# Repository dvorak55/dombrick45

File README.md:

# Dombrick45 : Dvorak Oriented 45% Keyboard

Dombrick45 is self made dvorak oriented keyboard.  
Dombrick45はDvorak配列志向の自作キーボードです。

"Dombrick" stands for Dvorak Oriented Mechanical Breakthough Remakable Interesting Coolest Keyboard (joke  
Dombrickという名前は「Dvorak志向の革新的で驚くべき大変興味深い最高にクールな機械式キーボード」を表す英単語の頭文字を取って命名しました（笑

Actually, "Dombri" means one of a japanese food style bowl, "ck" means nothing.  
嘘です、Dombriはもちろん日本語の丼を意味しており、ckの二文字はバランスを整えるために付けているだけです。

以下、[DescriptionのPDF](https://github.com/dvorak55/dombrick45/blob/master/description.pdf)から抜粋

## 概要
Dombrick45はコンパクトでシンプルな45％キーボードです。MCUもハンダ付けするタイプで比較的難易度は高め。QMK準拠、カスタマイズ可能。

## 特徴
- ボトムプレートがKitに含まれているため、キースイッチ・キーキャップとケーブルだけ揃えればキーボードが完成します
- 横幅13.25U、カーソルキーも搭載可能、USB Mini-BとUSB-Cの両対応
- 最下段キーがHotSwapで43keyから48keyまで好きに選べる。6.25uスペースバーも搭載可能
- ネジ締めは一切不要。モビロンバンドとシリコンマットによる全く新しいマウント方式なので組立しやすい
- ボトムプレートが重いので打鍵感が安定しています
- ATmega32U4やUSB-C端子のはんだ付けが必要。部品はすべて表面実装なので難易度は比較的高め
- 40%キーボード用キーキャップを使用(サンプルはGMK Jamón Forties)

## Kitに入っている部品
1. PCB 1枚
2. 電子部品(コンデンサ 7個、ダイオード 50個、フューズ 1個、抵抗 6個、ESDダイオード 1個、水晶振動子 1個、リセットスイッチ 1個)
3. MCU(ATmega32U4 1個)
4. USB端子(USB Mini-B 1個、USB-C 1個)
5. PCBソケット(Cherry MX互換 13個)
6. スタビライザー(2Uと6.25Uがそれぞれ 1個ずつ)
7. モビロンゴム(55mm 12本、100mm 6本)
8. シリコンシート(基板サイズ 2枚分)
9. ボトムプレート(厚さ2mmステンレス、基板サイズ 1枚)
10. プラスチックテープ(ソケットを隠すのに十分な長さ)
11. リセットスイッチを押す薄いプラ板

## 別途ご用意頂く部品
1. キースイッチ(Cherry MX互換で5ピンPCBマウント) 48個
2. キーキャップ
3. USBケーブル

## スペック（実装例）
サイズ：77mm × 253mm × 23mm

重さ　：約560グラム

## スイッチ互換性
Cherry MX互換とALPS(ただし最下段キーはCherry MX互換のみ)

## 写真等
### 実装例１

現在作者が使っているキー配列（48キー）。 GMK Paperworkを用いてさえ足りないキーキャップがある
### 実装例２

43キーしかない配列。6.25uのスペースバーを使えるようにしたかったんだ。

ちなみに最下段の両端のキーは取り外して、見えるはずの穴は赤色のプラスチックテープで巧妙に見えなくなっているので違和感が（多分）ないはず
### 実装例３

参考までに。無刻印は味気ない気がした。
### PCB基板（Ver.1かつJLCPCB版）

5枚のみ発注したJLCPCB版。ラーメンが食べたくなるでしょう？

Ver.1はこの5枚とALLPCBから届いた6枚、計11枚あります。
### スイッチ実装写真

右下と左下に赤色のプラスチックテープが貼ってあります。分かるかな〜

## Build Guide　ビルドガイド
部品をすべて実装するとこんな感じになります。

さぁ、あなたの丼を実装する素晴らしい一日をスタートしましょう！

### 多分必要な道具
- はんだごて　30ワットあればOK
- ハンダを拭くスポンジとはんだごて置き場
- ハンダ吸い取り器、ハンダ吸い取り線
- 鉛フリーではない普通のハンダ
- 無洗浄フラックス
- フラックスを洗浄するアルコール的なもの（ケンエーIPAとか）
- ピンセットがあると最高に便利
- 導通確認やショート確認のためのテスター
- カッター
- カッターマット

### 実装手順
1. 以下にあげた表面実装部品を基板PCBにすべてはんだ付けします。Kitの部品にはすべて部品番号が明示されています。また、PCB基板上のはんだ付けする場所に部品番号が印刷されています。すなわち、部品番号ごとに取り出した部品を、その番号の書かれた場所にはんだ付けすればOKです。ここで実装する部品は、向きが関係無い部品、もしくは向きを間違える心配のない部品です。
   - コンデンサ 7個　C1〜C7
   - ヒューズ 1個　F1
   - 抵抗 6個　R1〜R6
   - リセットスイッチ 1個　※4つ足のスイッチ　SW1
   - USB端子 2個　※USB-CとUSB-MiniBの2種類　USB1、USB2
   - ESDダイオード 1個　※4つ足の黒い部品　1本だけ足が広い。基板実装箇所でも1箇所だけ足が広い。　U2  
部品をすべて実装した写真の拡大バージョンです。こちらも参考にしてください↓

2. MCU 1個と水晶振動子 1個をはんだ付けします。向きに注意。
   - MCUの○印の位置と、PCB基板上の⚡印の位置が同じになるようにします
   - 水晶振動子は非常にわかりにくいですが、MCUから見て文字が読める向きに付けます。
MCUと水晶振動子の向きは以下の写真も参照してください↓

3. 上記部品がはんだ付け終わったら、パソコンとUSBケーブルで接続し、Dombrick45のファームウェアが書き込めるかを確認します。書き込めれば次に進み、書き込めない or 認識されなければ、はんだ付けを修正します。  
※ファームウェアを書き込む方法はこちらを参照下さい→　https://github.com/dvorak55/dombrick45/tree/master/qmk
4. ダイオードをはんだ付けします。向きはすべて線の書いてある方向が下になるようにします。スペースバーのある方が下、USB-MiniB端子のある方が上です。2個余るはずです（2個は予備です）。向きは以下の写真も参考にしてください。

5. PCBソケットをはんだ付けします。ソケットをPCB基板に差し込んでから、ハンダを付けてください。
6. 最後にキースイッチをはんだ付けします。
7. PCBソケットをはんだ付けした最下段にキースイッチを差し込みます。スペースバーのスタビライザーも取り付けます。
8. シリコンシートを基板のサイズに切り取ります。付属のシリコンシートから基板のサイズ2枚分取れます。これはPCB基板とボトムプレートの間に敷く衝撃吸収材兼絶縁材です。基板サイズのシリコンシートを2枚そのまま重ねるも良し、1枚を3分の2のところで分割し、上は3枚、中央は2枚、下は1枚と階段状にすることでキーボードに若干の角度を付けるも良し。
シリコンシートは付属のボトムプレートのサイズに切り取ります。

USB端子のある場所は、シリコンシートに切り欠けを作り、端子が干渉しないようにします。

2枚分のシリコンシートを階段状にする場合、以下のように切り欠けが重なるようにします。

このままだとリセットスイッチとシリコンシートが干渉し、強くキーを押すとリセットスイッチが押されてしまいます。そこで、リセットスイッチの位置（以下の画像の白い所）にも切り欠けを作ります。これは一番上に重ねたシートのみでOKです。

切り欠けを作ったシート

最終的にできたシートを重ねた状態

9. 基板・シリコンシート・ボトムプレートを重ねます。
10. それらをモビロンゴムでまとめます。短いモビロンゴムは縦方向、長いモビロンゴムは横方向をとめます。うまくキースイッチの間に入るようにゴムを調整します。短いゴムは4本、長いゴムは2本で足ります。残りは予備です。このゴムは滑り止めにもなっています。  
ゴムは以下の写真の線のところに配置すると良さげです。横方向の一番上はあってもなくても大丈夫です。

短いゴムはそのまま付けるだけだとキーキャップに干渉します。

適当なキーキャップを取り外し、

先の尖っていない細い棒等でモビロンゴムを一番下まで突っつきます。

4箇所ともゴムをきちんと一番下まで入れます。

横方向のゴムを付けるのは簡単だと思います。3本付けるとこのようになります。

11. お好きなキーキャップを取り付けます
12. もし43キーか46キーのキーマップを実装していた場合、最下段両端のキーソケットと穴を隠すために、Kitの袋に貼り付いている赤色のプラスチックテープを適当に切りPCB基板の最下段両端部分を隠すように貼ります。
13. お好きなUSBケーブルでパソコンに接続します
14. リセットスイッチが右手小指辺りにあります。リセットスイッチを押すための薄いプラ板をシリコンシートとPCB基板の間に挿入し、リセットスイッチを押してください  
この辺りに板を差し込みます。

リセットスイッチは以下の写真の黄色丸の位置にあります。板をこの辺りにまで差し込み、キーボードを押してリセットスイッチを押します。

15. リセットスイッチを押したら、ファームウェアを書き込み、動作確認を行う  
ファームウェアを書き込む方法はこちらを参照下さい→　https://github.com/dvorak55/dombrick45/tree/master/qmk

### 完成です！
楽しい丼生活をエンジョイしてください！

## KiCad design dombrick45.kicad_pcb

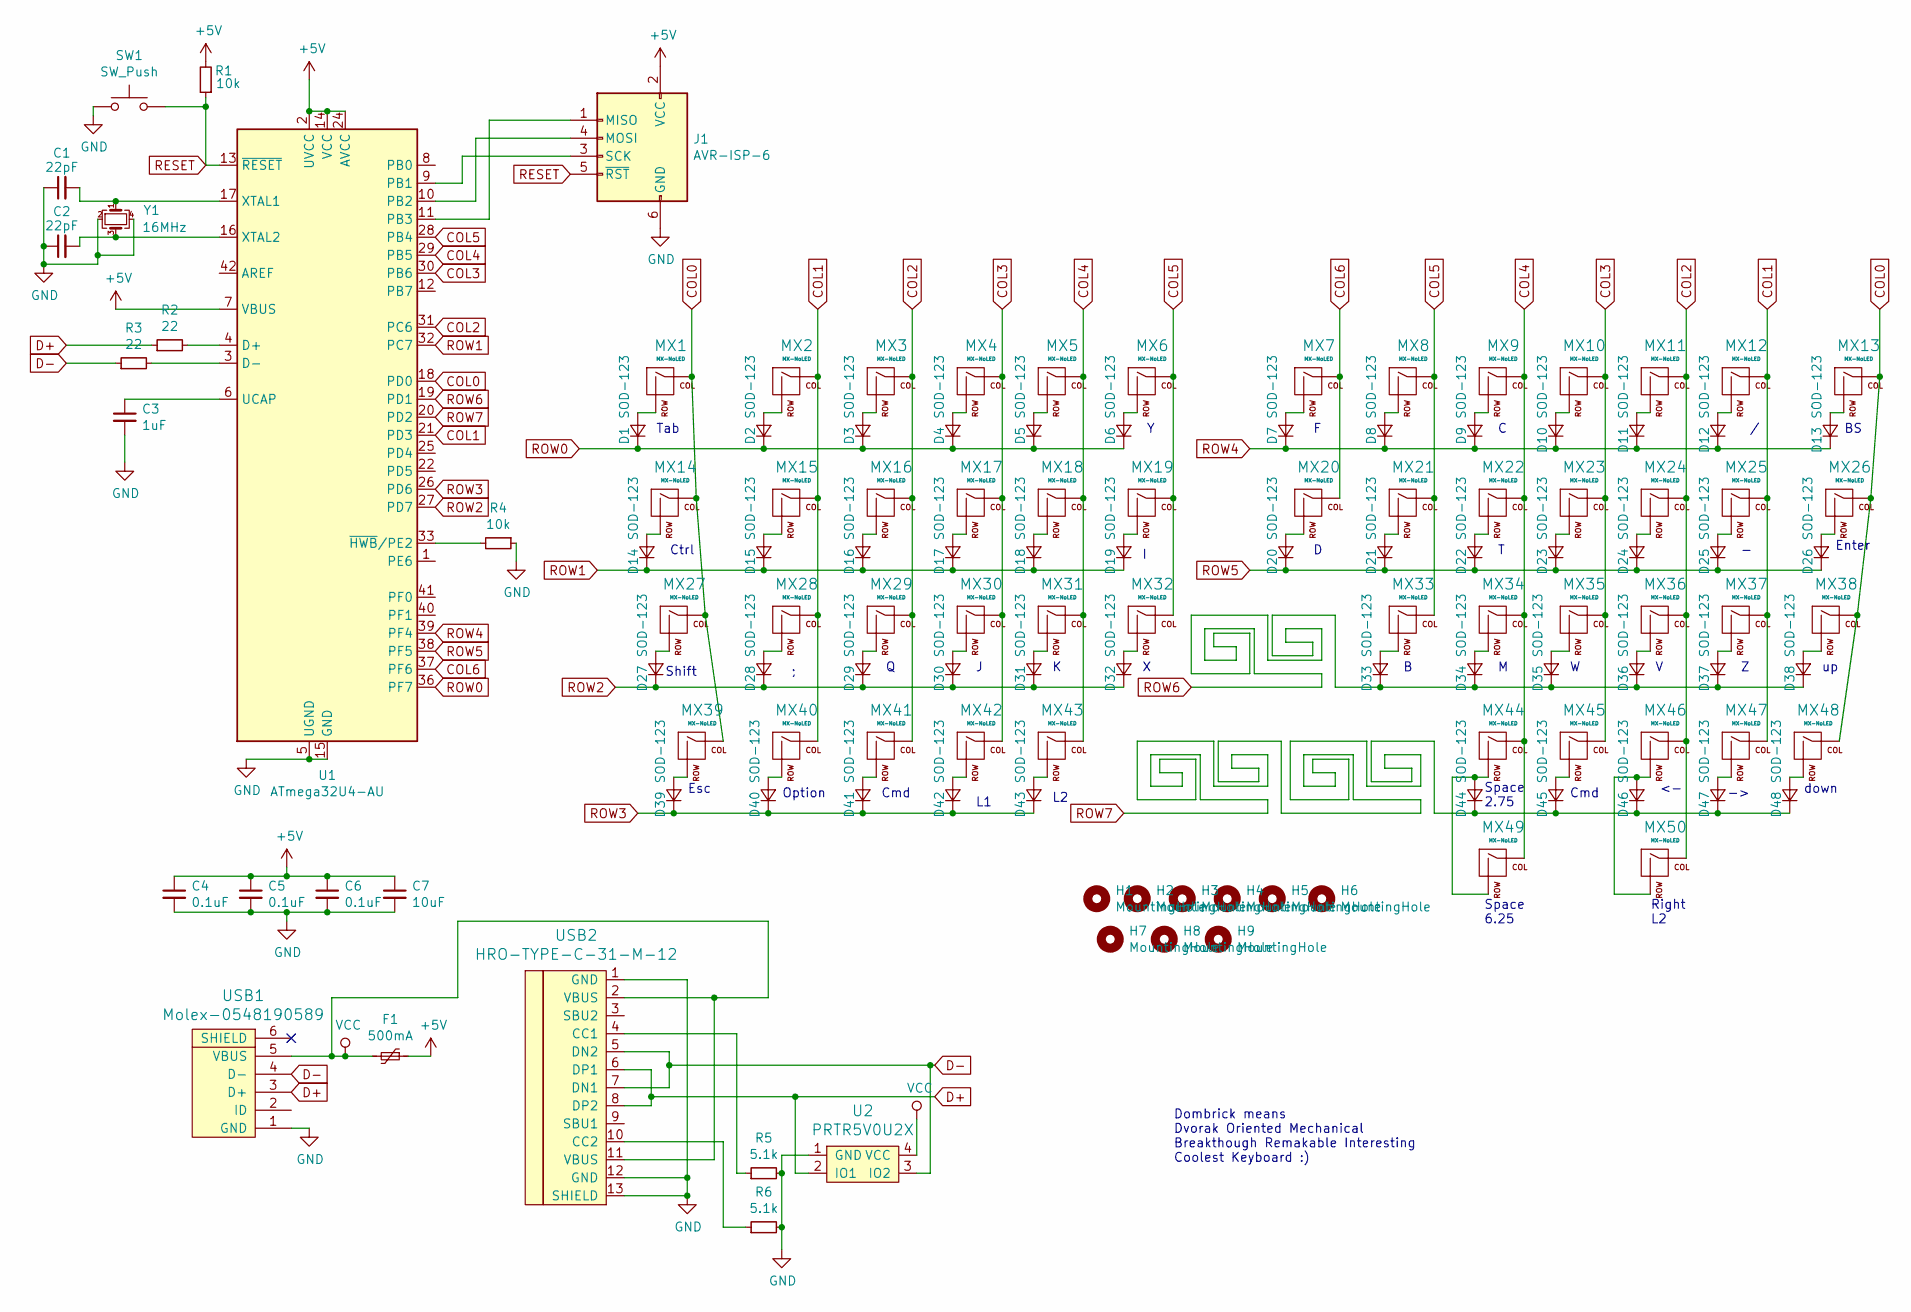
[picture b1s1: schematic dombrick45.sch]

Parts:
C1, C2: 22pF; C_0805_2012Metric_Pad1.15x1.40mm_HandSolder
C3: 1uF; C_0805_2012Metric_Pad1.15x1.40mm_HandSolder
C4, C5, C6: 0.1uF; C_0805_2012Metric_Pad1.15x1.40mm_HandSolder
C7: 10uF; C_0805_2012Metric_Pad1.15x1.40mm_HandSolder
D1, D2, D3, D4, D5, D6, D7, D8, D9, D10, D11, D12, D13, D14, D15, D16, D17, D18, D19, D20, D21, D22, D23, D24, D25, D26, D27, D28, D29, D30, D31, D32, D33, D34, D35, D36, D37, D38, D39, D40, D41, D42, D43, D44, D45, D46, D47, D48: SOD-123; D_SOD-123
F1: 500mA; Fuse_1206_3216Metric
H1, H2, H3, H4, H5, H6, H7, H8, H9: MountingHole; MountingHole_2.2mm_M2
J1: AVR-ISP-6; Reset_Pretty
MX1, MX2, MX3, MX4, MX5, MX6, MX7, MX8, MX9, MX10, MX11, MX12, MX15, MX16, MX17, MX18, MX19, MX20, MX21, MX22, MX23, MX24, MX25, MX26, MX28, MX29, MX30, MX31, MX32, MX33, MX34, MX35, MX36, MX37, MX38: MX-NoLED; MX-1U-NoLED
MX13, MX14, MX27: MX-NoLED; MX-1.25U-NoLED
MX39, MX40, MX46, MX47, MX48: MX-NoLED; MXOnly-1U-Hotswap
MX41, MX42, MX43, MX45, MX50: MX-NoLED; MXOnly-1.25U-Hotswap
MX44: MX-NoLED; MXOnly-2.75U-Hotswap
MX49: MX-NoLED; MXOnly-6.25U-Hotswap-ReversedStabilizers
R1, R4: 10k; R_0805_2012Metric
R2, R3: 22; R_0805_2012Metric
R5, R6: 5.1k; R_0805_2012Metric
SW1: SW_Push; SKQG-1155865
U1: ATmega32U4-AU; TQFP-44_10x10mm_P0.8mm
U2: PRTR5V0U2X; SOT143B
USB1: Molex-0548190589
USB2: HRO-TYPE-C-31-M-12; HRO-TYPE-C-31-M-12-Assembly
Y1: 16MHz; Crystal_SMD_3225-4Pin_3.2x2.5mm

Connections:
+5V: C4.1, C5.1, C6.1, C7.1, F1.1, J1.2 (VCC), R1.2, U1.2 (UVCC), U1.7 (VBUS), U1.14 (VCC), U1.24 (AVCC), U1.34 (VCC), U1.44 (AVCC)
COL0: MX1.1 (COL), MX13.1 (COL), MX14.1 (COL), MX26.1 (COL), MX27.1 (COL), MX38.1 (COL), MX39.1 (COL), MX48.1 (COL), U1.18 (PD0)
COL1: MX2.1 (COL), MX12.1 (COL), MX15.1 (COL), MX25.1 (COL), MX28.1 (COL), MX37.1 (COL), MX40.1 (COL), MX47.1 (COL), U1.21 (PD3)
COL2: MX3.1 (COL), MX11.1 (COL), MX16.1 (COL), MX24.1 (COL), MX29.1 (COL), MX36.1 (COL), MX41.1 (COL), MX46.1 (COL), MX50.1 (COL), U1.31 (PC6)
COL3: MX4.1 (COL), MX10.1 (COL), MX17.1 (COL), MX23.1 (COL), MX30.1 (COL), MX35.1 (COL), MX42.1 (COL), MX45.1 (COL), U1.30 (PB6)
COL4: MX5.1 (COL), MX9.1 (COL), MX18.1 (COL), MX22.1 (COL), MX31.1 (COL), MX34.1 (COL), MX43.1 (COL), MX44.1 (COL), MX49.1 (COL), U1.29 (PB5)
COL5: MX6.1 (COL), MX8.1 (COL), MX19.1 (COL), MX21.1 (COL), MX32.1 (COL), MX33.1 (COL), U1.28 (PB4)
COL6: MX7.1 (COL), MX20.1 (COL), U1.37 (PF6)
D+: R2.1, U2.2 (IO1), USB1.3 (D+), USB2.6 (DP1), USB2.8 (DP2)
D-: R3.1, U2.3 (IO2), USB1.4 (D-), USB2.5 (DN2), USB2.7 (DN1)
GND: C1.1, C2.1, C3.2, C4.2, C5.2, C6.2, C7.2, J1.6 (GND), R4.1, R5.2, R6.2, SW1.1, U1.5 (UGND), U1.15 (GND), U1.23 (GND), U1.35 (GND), U1.43 (GND), U2.1 (GND), USB1.1 (GND), USB2.1 (GND), USB2.12 (GND), USB2.13 (SHIELD), Y1.2, Y1.4
unnamed: C1.2, U1.17 (XTAL1), Y1.1
unnamed: C2.2, U1.16 (XTAL2), Y1.3
unnamed: C3.1, U1.6 (UCAP)
unnamed: D1.2 (A), MX1.2 (ROW)
unnamed: D2.2 (A), MX2.2 (ROW)
unnamed: D3.2 (A), MX3.2 (ROW)
unnamed: D4.2 (A), MX4.2 (ROW)
unnamed: D5.2 (A), MX5.2 (ROW)
unnamed: D6.2 (A), MX6.2 (ROW)
unnamed: D7.2 (A), MX7.2 (ROW)
unnamed: D8.2 (A), MX8.2 (ROW)
unnamed: D9.2 (A), MX9.2 (ROW)
unnamed: D10.2 (A), MX10.2 (ROW)
unnamed: D11.2 (A), MX11.2 (ROW)
unnamed: D12.2 (A), MX12.2 (ROW)
unnamed: D13.2 (A), MX13.2 (ROW)
unnamed: D14.2 (A), MX14.2 (ROW)
unnamed: D15.2 (A), MX15.2 (ROW)
unnamed: D16.2 (A), MX16.2 (ROW)
unnamed: D17.2 (A), MX17.2 (ROW)
unnamed: D18.2 (A), MX18.2 (ROW)
unnamed: D19.2 (A), MX19.2 (ROW)
unnamed: D20.2 (A), MX20.2 (ROW)
unnamed: D21.2 (A), MX21.2 (ROW)
unnamed: D22.2 (A), MX22.2 (ROW)
unnamed: D23.2 (A), MX23.2 (ROW)
unnamed: D24.2 (A), MX24.2 (ROW)
unnamed: D25.2 (A), MX25.2 (ROW)
unnamed: D26.2 (A), MX26.2 (ROW)
unnamed: D27.2 (A), MX27.2 (ROW)
unnamed: D28.2 (A), MX28.2 (ROW)
unnamed: D29.2 (A), MX29.2 (ROW)
unnamed: D30.2 (A), MX30.2 (ROW)
unnamed: D31.2 (A), MX31.2 (ROW)
unnamed: D32.2 (A), MX32.2 (ROW)
unnamed: D33.2 (A), MX33.2 (ROW)
unnamed: D34.2 (A), MX34.2 (ROW)
unnamed: D35.2 (A), MX35.2 (ROW)
unnamed: D36.2 (A), MX36.2 (ROW)
unnamed: D37.2 (A), MX37.2 (ROW)
unnamed: D38.2 (A), MX38.2 (ROW)
unnamed: D39.2 (A), MX39.2 (ROW)
unnamed: D40.2 (A), MX40.2 (ROW)
unnamed: D41.2 (A), MX41.2 (ROW)
unnamed: D42.2 (A), MX42.2 (ROW)
unnamed: D43.2 (A), MX43.2 (ROW)
unnamed: D44.2 (A), MX44.2 (ROW), MX49.2 (ROW)
unnamed: D45.2 (A), MX45.2 (ROW)
unnamed: D46.2 (A), MX46.2 (ROW), MX50.2 (ROW)
unnamed: D47.2 (A), MX47.2 (ROW)
unnamed: D48.2 (A), MX48.2 (ROW)
unnamed: J1.1 (MISO), U1.11 (PB3)
unnamed: J1.3 (SCK), U1.9 (PB1)
unnamed: J1.4 (MOSI), U1.10 (PB2)
unnamed: R2.2, U1.4 (D+)
unnamed: R3.2, U1.3 (D-)
unnamed: R4.2, U1.33 (~HWB~/PE2)
unnamed: R5.1, USB2.4 (CC1)
unnamed: R6.1, USB2.10 (CC2)
RESET: J1.5 (~RST), R1.1, SW1.2, U1.13 (~RESET)
ROW0: D1.1 (K), D2.1 (K), D3.1 (K), D4.1 (K), D5.1 (K), D6.1 (K), U1.36 (PF7)
ROW1: D14.1 (K), D15.1 (K), D16.1 (K), D17.1 (K), D18.1 (K), D19.1 (K), U1.32 (PC7)
ROW2: D27.1 (K), D28.1 (K), D29.1 (K), D30.1 (K), D31.1 (K), D32.1 (K), U1.27 (PD7)
ROW3: D39.1 (K), D40.1 (K), D41.1 (K), D42.1 (K), D43.1 (K), U1.26 (PD6)
ROW4: D7.1 (K), D8.1 (K), D9.1 (K), D10.1 (K), D11.1 (K), D12.1 (K), D13.1 (K), U1.39 (PF4)
ROW5: D20.1 (K), D21.1 (K), D22.1 (K), D23.1 (K), D24.1 (K), D25.1 (K), D26.1 (K), U1.38 (PF5)
ROW6: D33.1 (K), D34.1 (K), D35.1 (K), D36.1 (K), D37.1 (K), D38.1 (K), U1.19 (PD1)
ROW7: D44.1 (K), D45.1 (K), D46.1 (K), D47.1 (K), D48.1 (K), U1.20 (PD2)
VCC: F1.2, U2.4 (VCC), USB1.5 (VBUS), USB2.2 (VBUS), USB2.11 (VBUS)

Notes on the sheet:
Tab
Esc
Cmd
Option
Shift
Ctrl
Space 2.75
down
Enter
Dombrick means Dvorak Oriented Mechanical Breakthough Remakable Interesting Coolest Keyboard :)
Space 6.25
Right L2

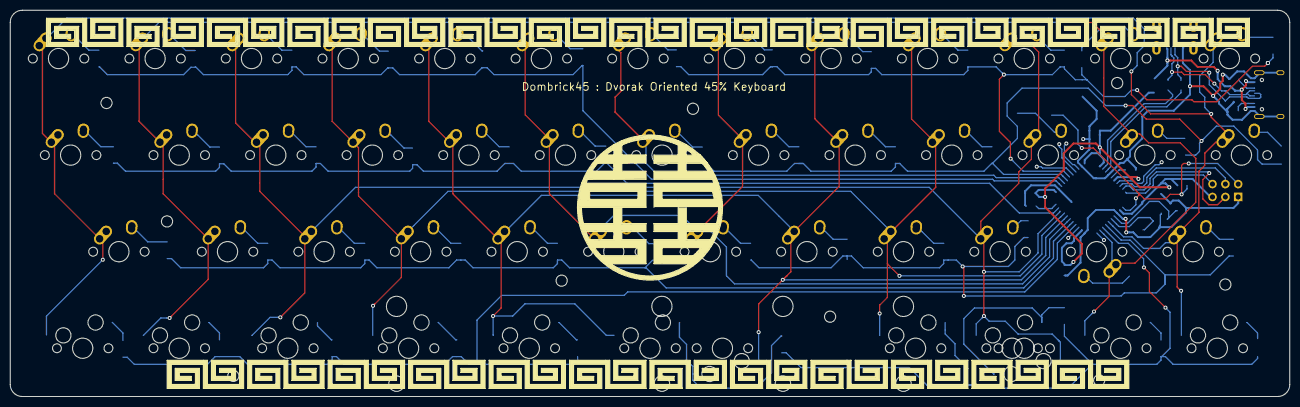
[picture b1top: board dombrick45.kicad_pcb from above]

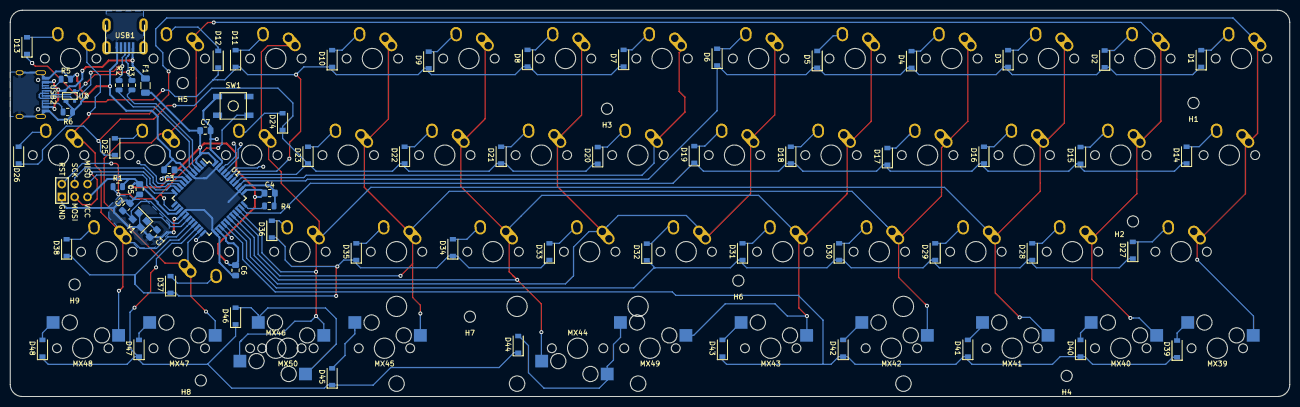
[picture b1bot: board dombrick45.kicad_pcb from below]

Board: 2 copper layers, 252.4 x 76.2 mm, 128 parts (78 on the bottom side), 80 nets.

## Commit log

2019-09-29 create kicad project
    only create project
2019-09-29 Add submodules
2019-09-30 add library
    add library
2019-09-30 ai03 wiki part3 70%
    neru
2019-10-05 2019-10-04
    2019-10-04 ai10さんブログの演習途中
2019-10-05 2019-10-06
2019-10-06 2019-10-06 tutorial
    hobo kansei
2019-10-06 2019-10-06 tutorial last
2019-10-08 dombrick45 sematic to pcb tochuu
2019-10-09 2019-10-10 keysw connect
2019-10-11 2019-10-12 PBC ver0.1
2019-10-12 2019-10-12 haisen bishuusei
2019-10-12 2019-10-12 advice itadaita ato
2019-10-13 2019-10-14 SPI toridashi and dombri mark
2019-10-18 2019-10-1
2019-10-20 2019-10-21 usb-c impl, gnd filled and silk design completed.
2019-10-21 2019-10-22 hobo OK
2019-10-23 2019-10-23 pcb to usb-c buhin hacchuu go
2019-10-26 2019-10-27 qmk dekitakamo
2019-11-03 2019-11-03 qmk-layout-png add
2019-11-04 2019-11-05 48keys firmware tukutta
2019-11-07 2019-11-07 all keymap teigi shita
2019-11-12 2019-11-13 qwerty keymap tukutta soshite description kaita
2019-11-13 2019-11-13 Description pdf tuika
2019-11-20 2019-11-20 Logo Add
2019-11-20 2019-11-20 image add
2019-11-20 update readme.md 2
2019-11-20 update readme.md 3
2019-11-21 2019-11-21 Build Guide Tukutteru
2019-11-22 2019-11-22 build guide img upload
2019-11-22 2019-11-22 Build Guide Daitai OK?
2019-11-22 aaaa
2019-11-22 aaaaa
2019-11-25 2019-11-25 perfect keylayout dekita to omou
2019-11-28 sonshi style description add
2019-11-28 2019-11-28 bishuusei
2019-11-28 2019-11-28 img seiri and description bishuusei
2020-03-22 update keymap hex
2020-03-22 キー配列の書き込み方法を記載
2020-03-22 ファームウェア書き込み方法を追記
2020-03-22 keymap update
2020-03-23 description.pdf update
